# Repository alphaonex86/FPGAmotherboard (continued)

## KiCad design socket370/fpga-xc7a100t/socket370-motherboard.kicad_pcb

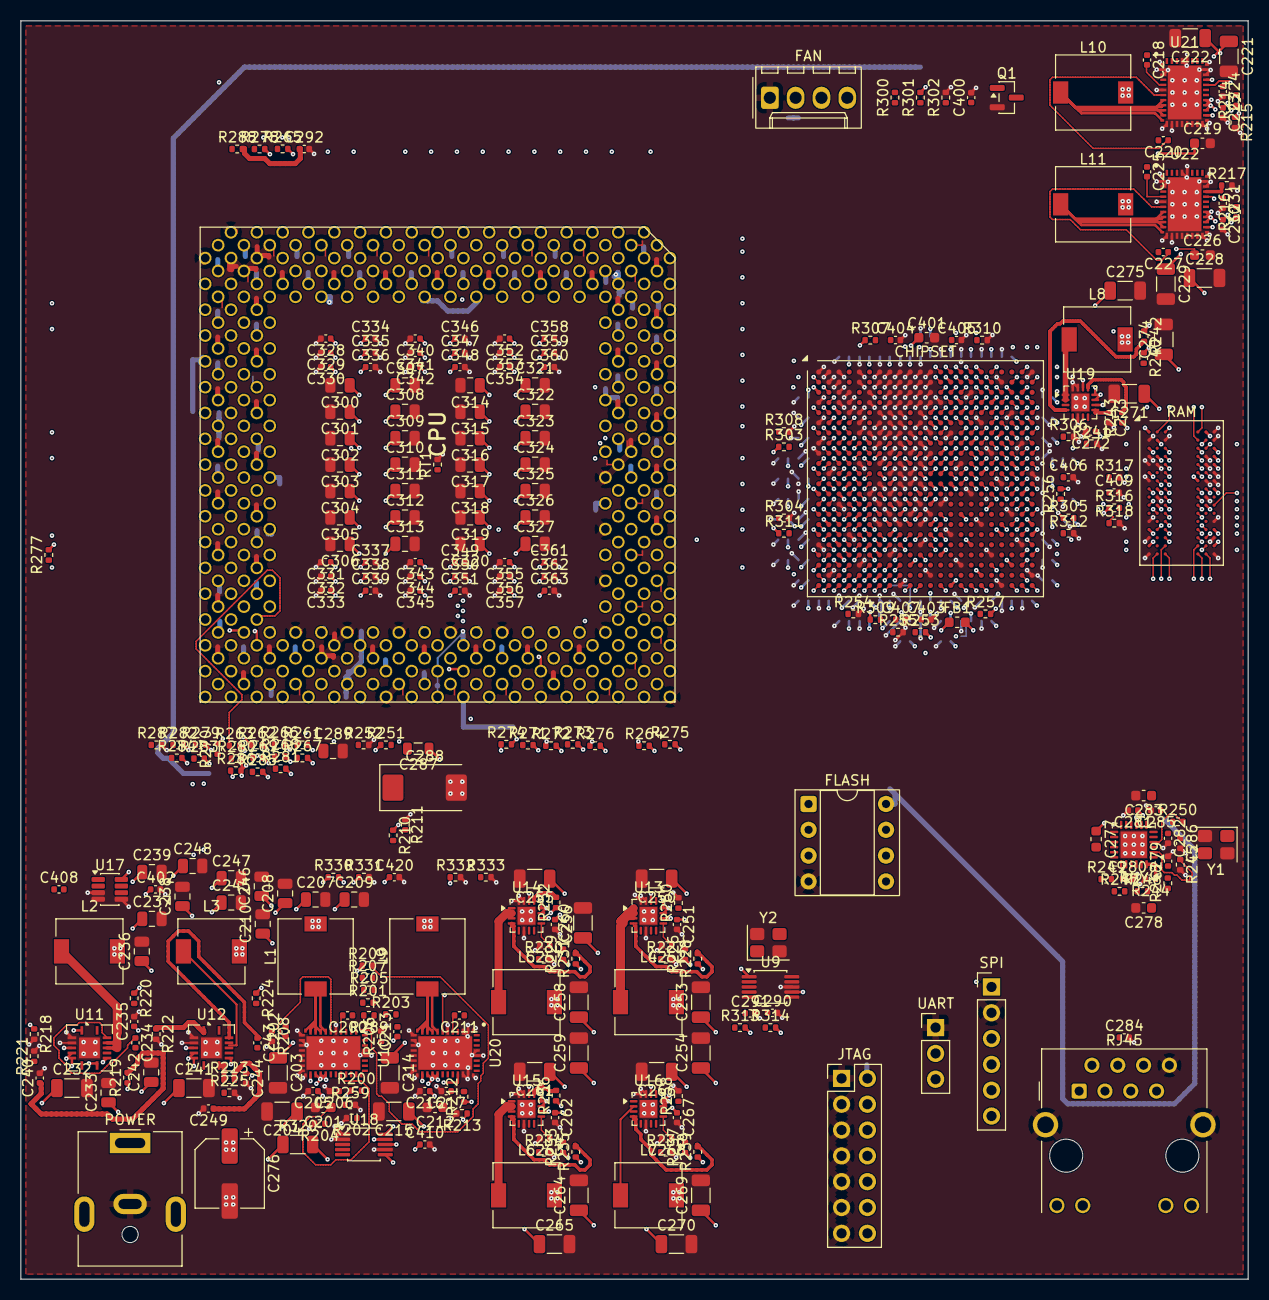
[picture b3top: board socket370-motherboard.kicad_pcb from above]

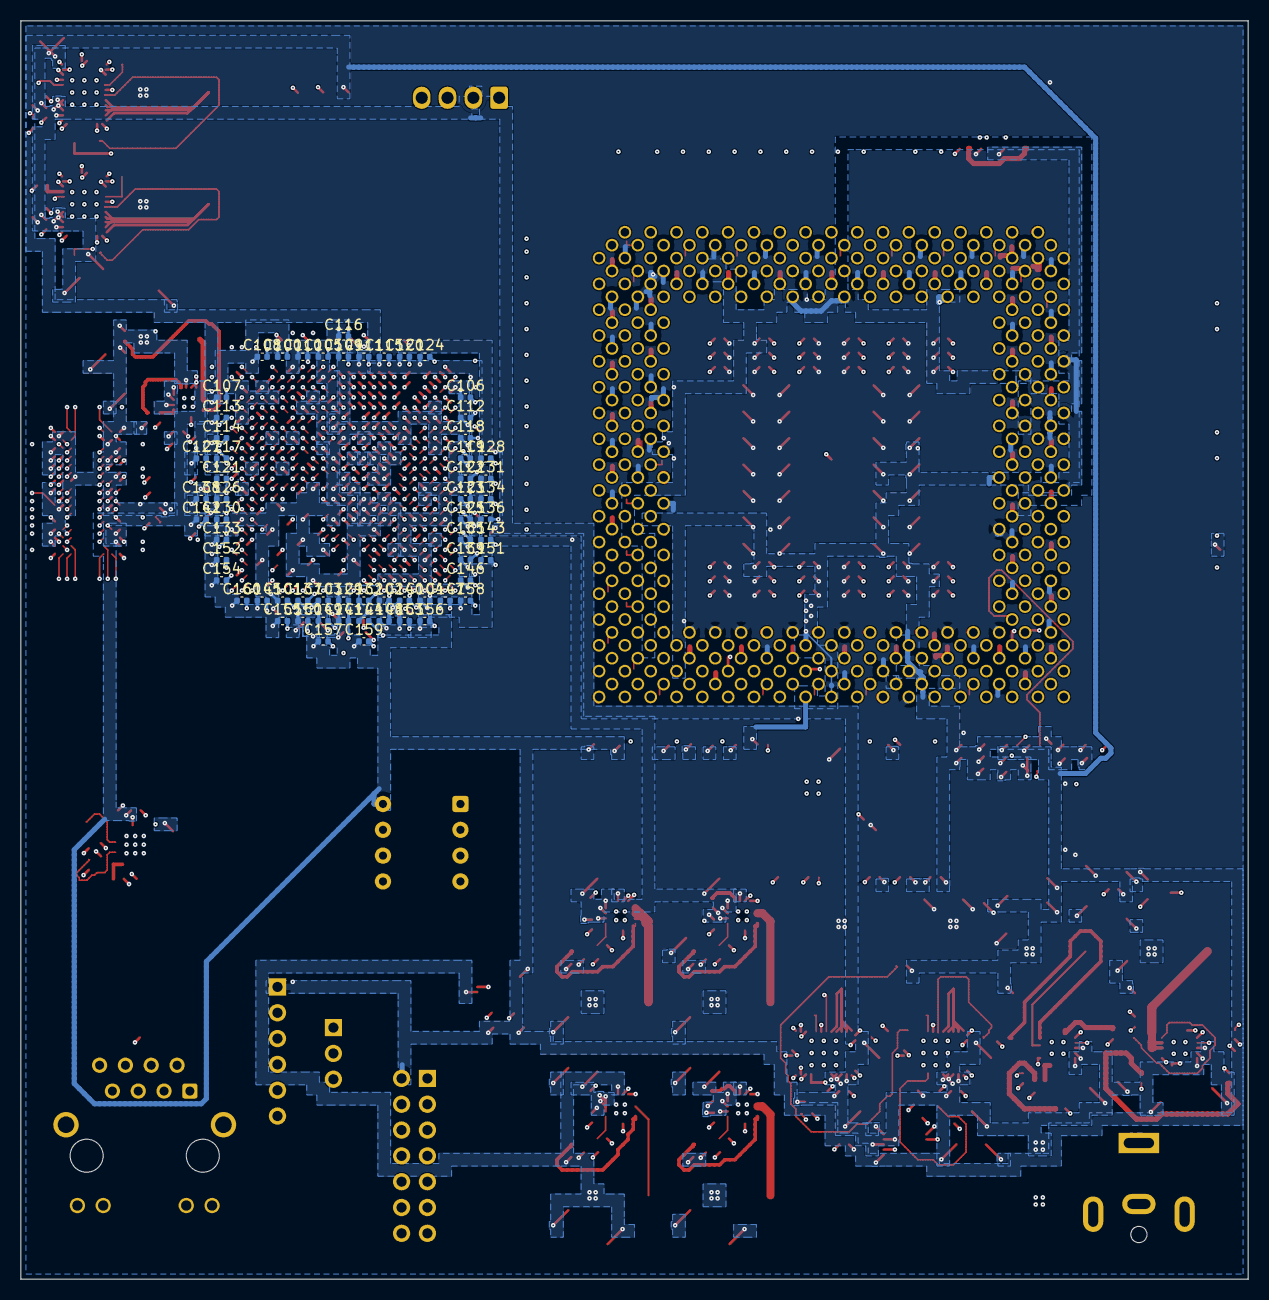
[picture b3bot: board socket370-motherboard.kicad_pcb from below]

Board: 8 copper layers, 120.8 x 123.8 mm, 384 parts (61 on the bottom side), 348 nets.

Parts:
C100, C101, C102, C103, C104, C105, C106, C107, C108, C109, C110, C111, C112, C113, C114, C115, C116, C117, C118, C119, C120, C121, C122, C123, C124, C125, C126, C127, C128, C129, C130, C131, C132, C133, C134, C135, C136, C137, C138, C139, C140, C141, C142, C143, C144, C145, C146, C147, C148, C149, C150, C151, C152, C153, C154, C155, C156, C157, C158, C159, C160: 470nF; C_0402_1005Metric
C200, C211, C218, C225: 1uF 16V X6S; C_0402_1005Metric
C201, C212, C219, C226: 4.7uF 16V X5R; C_0603_1608Metric
C202, C213, C220, C227: 100nF 16V X5R; C_0402_1005Metric
C203, C204, C214, C215, C221, C222, C228, C229, C232, C241, C250, C253, C254, C255, C258, C259, C260, C261, C264, C265, C266, C269, C270, C271, C274, C275: 22uF 25V X5R; C_1206_3216Metric
C205, C216, C223, C230, C235, C244, C403, C404, C405, C406, C407: 10nF 50V X7R; C_0402_1005Metric
C206, C217, C224, C231: 1uF 25V X5R; C_0402_1005Metric
C207, C208, C209, C210, C245, C246, C247, C248: 47uF 6.3V X5R; C_0805_2012Metric
C233, C242: 4.7uF 25V X7R; C_0805_2012Metric
C234, C243, C251, C256, C262, C267, C272, C279, C280, C281, C284, C402, C409, C410, C420: 100nF 16V X7R; C_0402_1005Metric
C236, C237, C238, C239: 47uF 10V X5R; C_0805_2012Metric
C240, C249: 8.2nF 50V X7R; C_0402_1005Metric
C252, C257, C263, C268, C273: 3.3nF 50V X7R; C_0402_1005Metric
C276: 100uF 25V; CP_Elec_6.3x7.7
C277: 600R@100MHz bead; L_0603_1608Metric
C278: 10uF 10V X5R; C_0603_1608Metric
C282: 470pF 50V C0G; C_0402_1005Metric
C283: 1uF 16V X7R; C_0603_1608Metric
C285, C286: 15pF 50V C0G; C_0402_1005Metric
C287: 4.7uH 30mA shielded; L_0805_2012Metric
C288: 33uF 20V tantalum; CP_EIA-7343-31_Kemet-D
C289: 4.7uF 16V X7R; C_0805_2012Metric
C290, C291: 4pF 50V C0G; C_0402_1005Metric
C292: 10pF 50V C0G; C_0402_1005Metric
C300, C301, C302, C303, C304, C305, C306, C307, C308, C309, C310, C311, C312, C313, C314, C315, C316, C317, C318, C319, C320, C321, C322, C323, C324, C325, C326, C327: 22uF; C_0805_2012Metric
C328, C329, C330, C331, C332, C333, C334, C335, C336, C337, C338, C339, C340, C341, C342, C343, C344, C345, C346, C347, C348, C349, C350, C351, C352, C353, C354, C355, C356, C357, C358, C359, C360, C361, C362, C363: 100nF; C_0402_1005Metric
C400: 1nF 50V C0G; C_0402_1005Metric
C401: 470nF 50V X7R; C_0603_1608Metric
C408: 100pF 50V C0G; C_0402_1005Metric
FB1: 600R@100MHz bead; L_0603_1608Metric
J1: HR911105A; RJ45_Hanrun_HR911105A_Horizontal
J2: PJ-063AH; BarrelJack_CUI_PJ-063AH_Horizontal
J3: JTAG; PinHeader_2x07_P2.54mm_Vertical
J4: UART; PinHeader_1x03_P2.54mm_Vertical
J5: SPI ISP; PinHeader_1x06_P2.54mm_Vertical
J6: fan 4-pin 1GND 2+12V 3TACH 4PWM; Molex_KK-254_AE-6410-04A_1x04_P2.54mm_Vertical
L1: VCORE ph1; L_7.3x7.3_H4.5
L2: 5V 6A; L_6.3x6.3_H3
L3: 3V3; L_6.3x6.3_H3
L4: VTT1V5; L_6.3x6.3_H3
L5: VCCINT1V0; L_6.3x6.3_H3
L6: VCCIO1V8; L_6.3x6.3_H3
L7: VCC2V5; L_6.3x6.3_H3
L8: 1V35 out; L_6.3x6.3_H3
L9: VCORE ph2; L_7.3x7.3_H4.5
L10: VCORE ph3; L_7.3x7.3_H4.5
L11: VCORE ph4; L_7.3x7.3_H4.5
Q1: BSS138; SOT-23
R200, R212, R214, R216: 10R 1%; R_0402_1005Metric
R201, R202: 17.8k 1%; R_0402_1005Metric
R203: 162k 1%; R_0402_1005Metric
R204, R215: 82.5k 1%; R_0402_1005Metric
R205, R237: 21.5k 1%; R_0402_1005Metric
R206, R208: 4.64k 1%; R_0402_1005Metric
R207: 1.27k 1%; R_0402_1005Metric
R209, R221, R225, R227, R230, R234, R238, R241, R245, R264, R301, R302, R305, R309, R313, R314: 10k 1%; R_0402_1005Metric
R210: 140R 1%; R_0402_1005Metric
R211: 0R; R_0402_1005Metric
R213: 8.25k 1%; R_0402_1005Metric
R217: 38.3k 1%; R_0402_1005Metric
R218, R222, R228, R231, R232, R235, R236, R239, R242, R243: 100k 1%; R_0402_1005Metric
R219, R223, R300: 1.69k 1%; R_0402_1005Metric
R220: 52.3k 1%; R_0402_1005Metric
R224: 31.6k 1%; R_0402_1005Metric
R226: 8.66k 1%; R_0402_1005Metric
R229, R308, R312: 2.49k 1%; R_0402_1005Metric
R233, R307: 12.4k 1%; R_0402_1005Metric
R240: 6.81k 1%; R_0402_1005Metric
R244: 12.1k 1%; R_0402_1005Metric
R246, R247, R248, R249: 49.9 1%; R_0402_1005Metric
R250, R258, R259, R260: 500R 1%; R_0402_1005Metric
R251, R252, R261, R266, R267, R268, R269, R270, R271, R272, R273, R274, R275, R279, R280, R281, R284, R285, R331: 150R 1%; R_0402_1005Metric
R253, R254, R255, R262, R263, R282, R286, R289, R316, R317: 1k 1%; R_0402_1005Metric
R256, R257, R303, R304, R306, R310: 4.02k 1%; R_0402_1005Metric
R265: 51R 1%; R_0402_1005Metric
R276, R283, R318: 240R 1%; R_0402_1005Metric
R277: 330R 1%; R_0402_1005Metric
R278: 91R 1%; R_0402_1005Metric
R287: 680R 1%; R_0402_1005Metric
R288: 22R 1%; R_0402_1005Metric
R311: 30.9k 1%; R_0402_1005Metric
R320: 10mR 1% 1W; R_1206_3216Metric
R330: 75R 1%; R_0402_1005Metric
R332, R333: 110R 1%; R_0402_1005Metric
RT1: 10k NTC 1% B3380; R_0402_1005Metric
U2: XC7A100T-2FGG484I; Xilinx_FGG484
U3: MT41K128M16JT-125; FBGA-96_8x14mm_Layout9x16_P0.8mm
U7: W25Q64JVDAIQ (DIP-8, socketed); DIP-8_W7.62mm_Socket
U8: LAN8720A-CP-TR; QFN-24-1EP_4x4mm_P0.5mm_EP2.6x2.6mm
U9: SI5351A-B-GTR; MSOP-10_3x3mm_P0.5mm
U10, U20, U21, U22: TPS546B24ARVFR; Texas_RVF0040A_LQFN-CLIP-40_5x7mm_P0.5mm
U11, U12: TPS54620RGYR; Texas_S-PVQFN-N14
U13, U14, U15, U16: TPS62130RGTR; QFN-16-1EP_3x3mm_P0.5mm_EP1.75x1.75mm
U17: TMP421AIDCNR; SOT-23-8
U18: INA226AIDGSR; MSOP-10_3x3mm_P0.5mm
U19: TPS62130RGTR 1V35; QFN-16-1EP_3x3mm_P0.5mm_EP1.75x1.75mm
XU1: PGA370 ZIF; PGA370_Socket_ZIF
Y1, Y2: 25MHz; Crystal_SMD_3225-4Pin_3.2x2.5mm

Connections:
+1V0: C115.1, C119.1, C120.1, C123.1, C124.1, C128.1, C129.1, C131.1, C135.1, C137.1, C139.1, C140.1, C143.1, C147.1, C148.1, C149.1, C153.1, C258.1, C259.1, C260.1, L5.2, R229.1, R231.1, U2.H8, U2.H10, U2.J7, U2.J9, U2.J11, U2.K8, U2.L7, U2.L11, U2.M8, U2.N7, U2.N11, U2.P8, U2.P10, U2.R7, U2.R9, U2.T8, U2.T10, U14.14
+1V8: C100.1, C102.1, C104.1, C105.1, C106.1, C107.1, C108.1, C109.1, C110.1, C112.1, C113.1, C116.1, C118.1, C122.1, C126.1, C132.1, C134.1, C136.1, C141.1, C144.1, C146.1, C151.1, C156.1, C158.1, C264.1, C265.1, FB1.1, L6.2, R233.1, R235.1, U2.A17, U2.AA7, U2.AB4, U2.B14, U2.C1, U2.C21, U2.D18, U2.E12, U2.E15, U2.F2, U2.F22, U2.H6, U2.H12, U2.J3, U2.K12, U2.M4, U2.M12, U2.N1, U2.P12, U2.R5, U2.R11, U2.T2, U2.V6, U2.W3, U15.14
+1V8_ADC: C125.1, C401.1, FB1.2, U2.K10
+1V35: C114.1, C117.1, C121.1, C127.1, C130.1, C138.1, C274.1, C275.1, L8.2, R240.1, R242.1, R316.1, U2.G19, U2.H16, U2.J13, U2.K20, U2.L17, U2.N21, U3.A1, U3.A8, U3.B2, U3.C1, U3.C9, U3.D2, U3.D9, U3.E9, U3.F1, U3.G7, U3.H2, U3.H9, U3.K2, U3.K8, U3.N1, U3.N9, U3.R1, U3.R9, U19.14
+2V5: C269.1, C270.1, L7.2, R237.1, R239.1, R251.1, R277.2, U9.7, U16.14, XU1.Z36 (VCC2.5)
+3V3: C101.1, C103.1, C111.1, C133.1, C142.1, C145.1, C150.1, C152.1, C154.1, C155.1, C157.1, C159.1, C160.1, C245.1, C246.1, C247.1, C248.1, C277.1, C281.1, C402.1, C410.1, J3.2, J5.1, L3.2, R209.1, R224.1, R253.2, R256.2, R257.2, R262.2, R263.2, R264.2, R301.2, R305.1, R309.1, R313.2, R314.2, U2.AA17, U2.AB14, U2.F12, U2.M14, U2.P18, U2.R15, U2.T12, U2.T22, U2.U8, U2.U19, U2.U22, U2.V16, U2.W13, U2.Y10, U2.Y20, U7.8, U8.9, U9.1, U17.8, U18.6
+5V: C236.1, C237.1, C238.1, C239.1, C250.1, C251.1, C255.1, C256.1, C261.1, C262.1, C266.1, C267.1, C271.1, C272.1, L2.2, R220.1, R232.1, R236.1, R243.1, R307.1, U13.10, U13.11, U13.12, U14.10, U14.11, U14.12, U15.10, U15.11, U15.12, U16.10, U16.11, U16.12, U19.10, U19.11, U19.12
+12V: C203.1, C204.1, C205.1, C214.1, C215.1, C216.1, C221.1, C222.1, C223.1, C228.1, C229.1, C230.1, C232.1, C233.1, C241.1, C242.1, C276.1, J6.2, R200.1, R212.1, R214.1, R216.1, R311.1, R320.2, U10.22, U10.23, U10.24, U10.25, U11.4, U11.5, U11.6, U12.4, U12.5, U12.6, U18.8, U18.9, U20.22, U20.23, U20.24, U20.25, U21.22, U21.23, U21.24, U21.25, U22.22, U22.23, U22.24, U22.25
+12V_IN: J2.1, R320.1, U18.10
GND: C100.2, C101.2, C102.2, C103.2, C104.2, C105.2, C106.2, C107.2, C108.2, C109.2, C110.2, C111.2, C112.2, C113.2, C114.2, C115.2, C116.2, C117.2, C118.2, C119.2, C120.2, C121.2, C122.2, C123.2, C124.2, C125.2, C126.2, C127.2, C128.2, C129.2, C130.2, C131.2, C132.2, C133.2, C134.2, C135.2, C136.2, C137.2, C138.2, C139.2, C140.2, C141.2, C142.2, C143.2, C144.2, C145.2, C146.2, C147.2, C148.2, C149.2, C150.2, C151.2, C152.2, C153.2, C154.2, C155.2, C156.2, C157.2, C158.2, C159.2, C160.2, C201.2, C203.2, C204.2, C205.2, C206.2, C207.2, C208.2, C209.2, C210.2, C212.2, C214.2, C215.2, C216.2, C217.2, C219.2, C221.2, C222.2, C223.2, C224.2, C226.2, C228.2, C229.2, C230.2, C231.2, C232.2, C233.2, C235.2, C236.2, C237.2, C238.2, C239.2, C240.2, C241.2, C242.2, C244.2, C245.2, C246.2, C247.2, C248.2, C249.2, C250.2, C251.2, C252.2, C253.2, C254.2, C255.2, C256.2, C257.2, C258.2, C259.2, C260.2, C261.2, C262.2, C263.2, C264.2, C265.2, C266.2, C267.2, C268.2, C269.2, C270.2, C271.2, C272.2, C273.2, C274.2, C275.2, C276.2, C278.2, C279.2, C280.2, C281.2, C282.2, C283.2, C284.2, C285.2, C286.2, C288.2, C289.2, C290.2, C291.2, C292.2, C300.2, C301.2, C302.2, C303.2, C304.2, C305.2, C306.2, C307.2, C308.2, C309.2, C310.2, C311.2, C312.2, C313.2, C314.2, C315.2, C316.2, C317.2, C318.2, C319.2, C320.2, C321.2, C322.2, C323.2, C324.2, C325.2, C326.2, C327.2, C328.2, C329.2, C330.2, C331.2, C332.2, C333.2, C334.2, C335.2, C336.2, C337.2, C338.2, C339.2, C340.2, C341.2, C342.2, C343.2, C344.2, C345.2, C346.2, C347.2, C348.2, C349.2, C350.2, C351.2, C352.2, C353.2, C354.2, C355.2, C356.2, C357.2, C358.2, C359.2, C360.2, C361.2, C362.2, C363.2, C400.2, C401.2, C402.2, C403.2, C404.2, C405.2, C406.2, C407.2, C409.2, C410.2, C420.2, J1.8, J1.SH, J2.2, J3.1, J3.3, J3.5, J3.7, J3.9, J3.11, J3.13, J4.1, J5.2, J6.1, Q1.2, R202.2, R204.2, R206.2, R208.2, R211.1, R213.2, R215.2, R217.2, R218.2, R221.2, R222.2, R225.2, R227.2, R230.2, R234.2, R238.2, R241.2, R244.2, R245.2, R252.2, R254.2, R255.2, R258.2, R259.2, R260.2, R287.2, R302.2, R304.2, R306.2, R308.2, R310.2, R312.2, R317.2, R318.2, R331.2, R332.2, R333.2, RT1.2, U2.A1, U2.A2, U2.A3, U2.A5, U2.A7, U2.A8, U2.A9, U2.A10, U2.A11, U2.A12, U2.A22, U2.AA2, U2.AA12, U2.AA22, U2.AB9, U2.AB19, U2.B2, U2.B3, U2.B5, U2.B7, U2.B8, U2.B9, U2.B10, U2.B11, U2.B12, U2.B19, U2.C3, U2.C4, U2.C6, U2.C8, U2.C9, U2.C10, U2.C11, U2.C12, U2.C16, U2.D1, U2.D3, U2.D4, U2.D6, U2.D8, U2.D9, U2.D10, U2.D11, U2.D12, U2.D13, U2.E4, U2.E5, U2.E7, U2.E8, U2.E9, U2.E11, U2.E20, U2.F1, U2.F5, U2.F7, U2.F8, U2.F9, U2.F11, U2.F17, U2.G5, U2.G6, U2.G7, U2.G8, U2.G9, U2.G10, U2.G12, U2.G14, U2.H1, U2.H7, U2.H9, U2.H11, U2.H21, U2.J1, U2.J8, U2.J10, U2.J12, U2.J18, U2.K5, U2.K7, U2.K9, U2.K11, U2.K15, U2.L2, U2.L8, U2.L9, U2.L10, U2.L22, U2.M7, U2.M9, U2.M10, U2.M11, U2.M19, U2.N6, U2.N8, U2.N16, U2.P3, U2.P7, U2.P9, U2.P11, U2.P13, U2.R8, U2.R10, U2.R12, U2.R20, U2.T7, U2.T9, U2.T11, U2.T17, U2.U4, U2.U14, U2.V1, U2.V11, U2.V21, U2.W8, U2.W18, U2.Y5, U2.Y15, U3.A9, U3.B1, U3.B3, U3.B9, U3.D1, U3.D8, U3.E1, U3.E2, U3.E8, U3.F9, U3.G1, U3.G8, U3.G9, U3.J2, U3.J8, U3.M1, U3.M9, U3.P1, U3.P9, U3.T1, U3.T9, U7.4, U8.25, U9.8, U10.6, U10.13, U10.14, U10.15, U10.16, U10.17, U10.18, U10.19, U10.20, U10.21, U10.36, U10.37, U10.41, U11.2, U11.3, U11.15, U12.2, U12.3, U12.15, U13.6, U13.15, U13.16, U13.17, U14.6, U14.15, U14.16, U14.17, U15.6, U15.15, U15.16, U15.17, U16.6, U16.15, U16.16, U16.17, U17.3, U17.4, U17.5, U18.1, U18.2, U18.7, U19.6, U19.15, U19.16, U19.17, U20.1, U20.2, U20.3, U20.6, U20.13, U20.14, U20.15, U20.16, U20.17, U20.18, U20.19, U20.20, U20.21, U20.30, U20.31, U20.32, U20.36, U20.37, U20.41, U21.1, U21.2, U21.3, U21.6, U21.13, U21.14, U21.15, U21.16, U21.17, U21.18, U21.19, U21.20, U21.21, U21.30, U21.31, U21.32, U21.36, U21.37, U21.41, U22.1, U22.2, U22.3, U22.6, U22.13, U22.14, U22.15, U22.16, U22.17, U22.18, U22.19, U22.20, U22.21, U22.30, U22.31, U22.32, U22.36, U22.37, U22.41, XU1.A37 (GND), XU1.AB32 (GND), XU1.AC5 (GND), XU1.AC33 (GND), XU1.AD2 (GND), XU1.AD34 (GND), XU1.AF32 (GND), XU1.AF36 (GND), XU1.AG5 (GND), XU1.AH2 (GND), XU1.AH34 (GND), XU1.AJ3 (GND), XU1.AJ7 (GND), XU1.AJ11 (GND), XU1.AJ15 (GND), XU1.AJ19 (GND), XU1.AJ23 (GND), XU1.AJ27 (GND), XU1.AK4 (GND), XU1.AK36 (GND), XU1.AL1 (GND), XU1.AL3 (GND), XU1.AM6 (GND), XU1.AM10 (GND), XU1.AM14 (GND), XU1.AM18 (GND), XU1.AM22 (GND), XU1.AM26 (GND), XU1.AM30 (GND), XU1.AM34 (GND), XU1.AN3 (GND), XU1.B4 (GND), XU1.B8 (GND), XU1.B12 (GND), XU1.B16 (GND), XU1.B20 (GND), XU1.B24 (GND), XU1.B28 (GND), XU1.B32 (GND), XU1.D2 (GND), XU1.D4 (GND), XU1.D18 (GND), XU1.D22 (GND), XU1.D26 (GND), XU1.D30 (GND), XU1.D34 (GND), XU1.E7 (GND), XU1.E11 (GND), XU1.E15 (GND), XU1.E19 (GND), XU1.F20 (GND), XU1.F24 (GND), XU1.F28 (GND), XU1.F32 (GND), XU1.F36 (GND), XU1.G5 (GND), XU1.H2 (GND), XU1.H34 (GND), XU1.K36 (GND), XU1.L5 (GND), XU1.M2 (GND), XU1.M34 (GND), XU1.P32 (GND), XU1.P36 (GND), XU1.Q5 (GND), XU1.R34 (GND), XU1.T32 (GND), XU1.T36 (GND), XU1.U5 (GND), XU1.V2 (GND), XU1.V34 (GND), XU1.X32 (GND), XU1.X36 (GND), XU1.Y5 (GND), XU1.Y37 (GND), XU1.Z2 (GND), XU1.Z34 (GND), Y1.2, Y1.4, Y2.2, Y2.4
VCORE: C207.1, C208.1, C209.1, C210.1, C287.1, C300.1, C301.1, C305.1, C306.1, C307.1, C308.1, C309.1, C311.1, C314.1, C315.1, C316.1, C317.1, C318.1, C319.1, C320.1, C321.1, C322.1, C323.1, C324.1, C325.1, C326.1, C327.1, C331.1, C333.1, C334.1, C335.1, C336.1, C338.1, C339.1, C340.1, C341.1, C342.1, C343.1, C344.1, C345.1, C346.1, C347.1, C348.1, C353.1, C354.1, C356.1, C357.1, C358.1, C359.1, C360.1, C361.1, C362.1, C363.1, L1.2, L9.2, L10.2, L11.2, R210.1, R265.2, R303.1, XU1.AA5 (VCCCORE), XU1.AA37 (VCCCORE), XU1.AB2 (VCCCORE), XU1.AB34 (VCCCORE), XU1.AD32 (VCCCORE), XU1.AE5 (VCCCORE), XU1.AF2 (VCCCORE), XU1.AF34 (VCCCORE), XU1.AH24 (VCCCORE), XU1.AH32 (VCCCORE), XU1.AH36 (VCCCORE), XU1.AJ5 (VCCCORE), XU1.AJ9 (VCCCORE), XU1.AJ13 (VCCCORE), XU1.AJ17 (VCCCORE), XU1.AJ21 (VCCCORE), XU1.AJ25 (VCCCORE), XU1.AJ29 (VCCCORE), XU1.AK2 (VCCCORE), XU1.AK34 (VCCCORE), XU1.AM4 (VCCCORE), XU1.AM8 (VCCCORE), XU1.AM12 (VCCCORE), XU1.AM16 (VCCCORE), XU1.AM20 (VCCCORE), XU1.AM24 (VCCCORE), XU1.AM28 (VCCCORE), XU1.AM32 (VCCCORE), XU1.B6 (VCCCORE), XU1.B10 (VCCCORE), XU1.B14 (VCCCORE), XU1.B18 (VCCCORE), XU1.B22 (VCCCORE), XU1.B26 (VCCCORE), XU1.B30 (VCCCORE), XU1.B34 (VCCCORE), XU1.C3 (VCCCORE), XU1.D6 (VCCCORE), XU1.D20 (VCCCORE), XU1.D24 (VCCCORE), XU1.D28 (VCCCORE), XU1.D32 (VCCCORE), XU1.D36 (VCCCORE), XU1.E5 (VCCCORE), XU1.E9 (VCCCORE), XU1.E13 (VCCCORE), XU1.E17 (VCCCORE), XU1.F2 (VCCCORE), XU1.F4 (VCCCORE), XU1.F14 (VCCCORE), XU1.F22 (VCCCORE), XU1.F26 (VCCCORE), XU1.F30 (VCCCORE), XU1.F34 (VCCCORE), XU1.H32 (VCCCORE), XU1.H36 (VCCCORE), XU1.J5 (VCCCORE), XU1.K2 (VCCCORE), XU1.K32 (VCCCORE), XU1.K34 (VCCCORE), XU1.M32 (VCCCORE), XU1.N5 (VCCCORE), XU1.P2 (VCCCORE), XU1.P34 (VCCCORE), XU1.R32 (VCCCORE), XU1.R36 (VCCCORE), XU1.S5 (VCCCORE), XU1.T2 (VCCCORE), XU1.T34 (VCCCORE), XU1.V32 (VCCCORE), XU1.V36 (VCCCORE), XU1.W5 (VCCCORE), XU1.Y35 (VCCCORE), XU1.Z32 (VCCCORE)
VREF1V0: C328.1, C329.1, C330.1, C352.1, C420.1, R330.2, R331.1, U2.C20, U2.D15, U2.E3, U2.N3, U2.V3, U2.W7, XU1.AD6 (VREF), XU1.AK12 (VREF), XU1.AK22 (VREF), XU1.E33 (VREF), XU1.F18 (VREF), XU1.K4 (VREF), XU1.R6 (VREF), XU1.V6 (VREF)
VTT1V5: C253.1, C254.1, C302.1, C303.1, C304.1, C310.1, C312.1, C313.1, C332.1, C337.1, C349.1, C350.1, C351.1, C355.1, L4.2, R226.1, R228.1, R261.2, R266.2, R267.2, R268.2, R269.2, R270.2, R271.2, R272.2, R273.2, R274.2, R275.2, R276.2, R278.2, R279.2, R280.2, R281.2, R282.2, R283.2, R284.2, R285.2, R286.2, R330.1, U13.14, XU1.AA33 (VTT), XU1.AA35 (VTT), XU1.AB36 (VCCCMOS), XU1.AD36 (VCC1), XU1.AH20 (VTT), XU1.AK16 (VTT), XU1.AL13 (VTT), XU1.AL21 (VTT), XU1.AN11 (VTT), XU1.AN15 (VTT), XU1.AN21 (VTT), XU1.E23 (VTT), XU1.G35 (VTT), XU1.S33 (VTT), XU1.S37 (VTT), XU1.U35 (VTT), XU1.U37 (VTT)
cpu_a20m_n: R261.1, U2.A21, XU1.AE33 (A20M#)
cpu_a[3]: U2.AA6, XU1.AK8 (A3#)
cpu_a[4]: U2.Y9, XU1.AH12 (A4#)
cpu_a[5]: U2.Y6, XU1.AH8 (A5#)
cpu_a[6]: U2.AB7, XU1.AN9 (A6#)
cpu_a[7]: U2.T6, XU1.AL15 (A7#)
cpu_a[8]: U2.V8, XU1.AH10 (A8#)
cpu_a[9]: U2.V7, XU1.AL9 (A9#)
cpu_a[10]: U2.V5, XU1.AH6 (A10#)
cpu_a[11]: U2.Y8, XU1.AK10 (A11#)
cpu_a[12]: U2.M6, XU1.AN5 (A12#)
cpu_a[13]: U2.AB5, XU1.AL7 (A13#)
cpu_a[14]: U2.E13, XU1.AK14 (A14#)
cpu_a[15]: U2.T5, XU1.AL5 (A15#)
cpu_a[16]: U2.W6, XU1.AN7 (A16#)
cpu_a[17]: U2.F4, XU1.AE1 (A17#)
cpu_a[18]: U2.J6, XU1.Z6 (A18#)
cpu_a[19]: U2.R4, XU1.AG3 (A19#)
cpu_a[20]: U2.U3, XU1.AC3 (A20#)
cpu_a[21]: U2.H4, XU1.AJ1 (A21#)
cpu_a[22]: U2.P4, XU1.AE3 (A22#)
cpu_a[23]: U2.K6, XU1.AB6 (A23#)
cpu_a[24]: U2.T4, XU1.AB4 (A24#)
cpu_a[25]: U2.L6, XU1.AF6 (A25#)
cpu_a[26]: U2.Y2, XU1.Y3 (A26#)
cpu_a[27]: U2.R2, XU1.AA1 (A27#)
cpu_a[28]: U2.W5, XU1.AK6 (A28#)
cpu_a[29]: U2.J5, XU1.Z4 (A29#)
cpu_a[30]: U2.L4, XU1.AA3 (A30#)
cpu_a[31]: U2.AB3, XU1.AD4 (A31#)
cpu_a[32]: U2.P5, XU1.X6 (A32#)
cpu_a[33]: U2.AA1, XU1.AC1 (A33#)
cpu_a[34]: U2.G4, XU1.W3 (A34#)
cpu_a[35]: U2.N5, XU1.AF4 (A35#)
cpu_ads_n: U2.E22, XU1.AN31 (ADS#)
cpu_bclk: U9.10, XU1.W37 (BCLK)
cpu_binit_n: U2.G21, XU1.B36 (BINIT#)
cpu_bnr_n: U2.C13, XU1.AH14 (BNR#)
cpu_bpri_n: U2.F15, XU1.AN17 (BPRI#)
cpu_br0_n: U2.F20, XU1.AN29 (BR0#)
cpu_bsel[0]: R262.1, XU1.AJ33 (BSEL)
cpu_bsel[1]: R263.1, XU1.AJ31 (BSEL)
cpu_clkref: C289.1, R251.2, R252.1, XU1.Y33 (CLKREF)
cpu_d[0]: U2.R1, XU1.W1 (D0#)
cpu_d[1]: U2.R3, XU1.T4 (D1#)
cpu_d[2]: U2.J2, XU1.N1 (D2#)
cpu_d[3]: U2.H5, XU1.M6 (D3#)
cpu_d[4]: U2.U1, XU1.U1 (D4#)
cpu_d[5]: U2.L3, XU1.S3 (D5#)
cpu_d[6]: U2.V4, XU1.T6 (D6#)
cpu_d[7]: U2.G2, XU1.J1 (D7#)
cpu_d[8]: U2.T1, XU1.S1 (D8#)
cpu_d[9]: U2.Y3, XU1.P6 (D9#)
cpu_d[10]: U2.K3, XU1.Q3 (D10#)
cpu_d[11]: U2.AB1, XU1.M4 (D11#)
cpu_d[12]: U2.G3, XU1.Q1 (D12#)
cpu_d[13]: U2.H2, XU1.L1 (D13#)
cpu_d[14]: U2.W1, XU1.N3 (D14#)
cpu_d[15]: U2.U2, XU1.U3 (D15#)
cpu_d[16]: U2.P2, XU1.H4 (D16#)
cpu_d[17]: U2.V2, XU1.R4 (D17#)
cpu_d[18]: U2.M3, XU1.P4 (D18#)
cpu_d[19]: U2.K4, XU1.H6 (D19#)
cpu_d[20]: U2.N2, XU1.L3 (D20#)
cpu_d[21]: U2.L1, XU1.G1 (D21#)
cpu_d[22]: U2.L5, XU1.F8 (D22#)
cpu_d[23]: U2.F3, XU1.G3 (D23#)
cpu_d[24]: U2.AB2, XU1.K6 (D24#)
cpu_d[25]: U2.K2, XU1.E3 (D25#)
cpu_d[26]: U2.E2, XU1.E1 (D26#)
cpu_d[27]: U2.R6, XU1.F12 (D27#)
cpu_d[28]: U2.H3, XU1.A5 (D28#)
cpu_d[29]: U2.P1, XU1.A3 (D29#)
cpu_d[30]: U2.M2, XU1.J3 (D30#)
cpu_d[31]: U2.Y1, XU1.C5 (D31#)
cpu_d[32]: U2.W2, XU1.F6 (D32#)
cpu_d[33]: U2.D2, XU1.C1 (D33#)
cpu_d[34]: U2.T3, XU1.C7 (D34#)
cpu_d[35]: U2.M1, XU1.B2 (D35#)
cpu_d[36]: U2.W4, XU1.C9 (D36#)
cpu_d[37]: U2.M5, XU1.A9 (D37#)
cpu_d[38]: U2.AA3, XU1.D8 (D38#)
cpu_d[39]: U2.Y4, XU1.D10 (D39#)
cpu_d[40]: U2.Y7, XU1.C15 (D40#)
cpu_d[41]: U2.AB6, XU1.D14 (D41#)
cpu_d[42]: U2.P6, XU1.D12 (D42#)
cpu_d[43]: U2.J4, XU1.A7 (D43#)
cpu_d[44]: U2.AA4, XU1.A11 (D44#)
cpu_d[45]: U2.U5, XU1.C11 (D45#)
cpu_d[46]: U2.A14, XU1.A21 (D46#)
cpu_d[47]: U2.U7, XU1.A15 (D47#)
cpu_d[48]: U2.V9, XU1.A17 (D48#)
cpu_d[49]: U2.U6, XU1.C13 (D49#)
cpu_d[50]: U2.F16, XU1.C25 (D50#)
cpu_d[51]: U2.B17, XU1.A13 (D51#)
cpu_d[52]: U2.AA8, XU1.D16 (D52#)
cpu_d[53]: U2.A15, XU1.A23 (D53#)
cpu_d[54]: U2.D14, XU1.C21 (D54#)
cpu_d[55]: U2.B13, XU1.C19 (D55#)
cpu_d[56]: U2.A18, XU1.C27 (D56#)
cpu_d[57]: U2.A13, XU1.A19 (D57#)
cpu_d[58]: U2.C15, XU1.C23 (D58#)
cpu_d[59]: U2.W9, XU1.C17 (D59#)
cpu_d[60]: U2.D16, XU1.A25 (D60#)
cpu_d[61]: U2.E17, XU1.A27 (D61#)
cpu_d[62]: U2.C17, XU1.E25 (D62#)
cpu_d[63]: U2.AB8, XU1.F16 (D63#)
cpu_dbsy_n: U2.E19, XU1.AL27 (DBSY#)
cpu_defer_n: U2.AA5, XU1.AN19 (DEFER#)
cpu_drdy_n: U2.F19, XU1.AN27 (DRDY#)
cpu_edgctrl: R265.1, XU1.AG1 (EDGCTRL)
cpu_ferr_n: R266.1, U2.F21, XU1.AC35 (FERR#)
cpu_flush_n: R267.1, U2.B22, XU1.AE37 (FLUSH#)
cpu_hit_n: U2.F18, XU1.AL25 (HIT#)
cpu_hitm_n: U2.E18, XU1.AL23 (HITM#)
cpu_ierr_n: R268.1, U2.D22, XU1.AE35 (IERR#)
cpu_ignne_n: R269.1, U2.G22, XU1.AG37 (IGNNE#)
cpu_init_n: R270.1, U2.B20, XU1.AG33 (INIT#)
cpu_lint0: R271.1, U2.F14, XU1.M36 (LINT0/INTR)
cpu_lint1: R272.1, XU1.L37 (LINT1/NMI)
cpu_lock_n: U2.D17, XU1.AK20 (LOCK#)
cpu_picclk: U9.6, XU1.J33 (PICCLK)
cpu_picd[0]: R273.1, XU1.J35 (PICD)
cpu_picd[1]: R274.1, XU1.L35 (PICD)
cpu_pll: C287.2, C288.1, XU1.U33 (PLL), XU1.W33 (PLL)
cpu_prdy_n: R275.1, XU1.A35 (PRDY#)
cpu_preq_n: R276.1, XU1.J37 (PREQ#)
cpu_pres_n: R264.1, XU1.C37 (CPUPRES#)
cpu_pwrgood: R277.1, U2.F13, XU1.AK26 (PWRGOOD)
cpu_req[0]: U2.B16, XU1.AK18 (REQ0#)
cpu_req[1]: U2.E14, XU1.AH16 (REQ1#)
cpu_req[2]: U2.A16, XU1.AH18 (REQ2#)
cpu_req[3]: U2.E16, XU1.AL19 (REQ3#)
cpu_req[4]: U2.B15, XU1.AL17 (REQ4#)
cpu_reset_n: R278.1, R288.1, U2.N4, XU1.AH4 (RESET#), XU1.X4 (RESET2#)
cpu_reset_rc: C292.1, R288.2
cpu_rs[0]: U2.D19, XU1.AH26 (RS0#)
cpu_rs[1]: U2.B18, XU1.AH22 (RS1#)
cpu_rs[2]: U2.D20, XU1.AK28 (RS2#)
cpu_rttctrl: R332.1, XU1.S35 (RTTCTRL)
cpu_slewctrl: R333.1, XU1.E27 (SLEWCTRL)
cpu_slp_n: R279.1, U2.C14, XU1.AH30 (SLP#)
cpu_smi_n: R280.1, U2.D21, XU1.AJ35 (SMI#)
cpu_stpclk_n: R281.1, U2.E21, XU1.AG35 (STPCLK#)
cpu_tck: R282.1, XU1.AL33 (TCK)
cpu_tdi: R283.1, XU1.AN35 (TDI)
cpu_tdo: R284.1, XU1.AN37 (TDO)
cpu_thermdn: C408.2, U17.2, XU1.AL29 (THERMDN)
cpu_thermdp: C408.1, U17.1, XU1.AL31 (THERMDP)
cpu_thermtrip_n: R285.1, U2.C18, XU1.AH28 (THERMTRIP#)
cpu_tms: R286.1, XU1.AK32 (TMS)
cpu_trdy_n: U2.C19, XU1.AN25 (TRDY#)
cpu_trst_n: R287.1, XU1.AN33 (TRST#)
ddr3_a[0]: U2.J17, U3.N3
ddr3_a[1]: U2.L16, U3.P7
ddr3_a[2]: U2.K16, U3.P3
ddr3_a[3]: U2.L13, U3.N2
ddr3_a[4]: U2.M16, U3.P8
ddr3_a[5]: U2.J16, U3.P2
ddr3_a[6]: U2.K14, U3.R8
ddr3_a[7]: U2.J15, U3.R2
ddr3_a[8]: U2.M13, U3.T8
ddr3_a[9]: U2.L15, U3.R3
ddr3_a[10]: U2.N19, U3.L7
ddr3_a[11]: U2.L19, U3.R7
ddr3_a[12]: U2.K17, U3.N7
ddr3_a[13]: U2.K13, U3.T3
ddr3_a[14]: U2.N18, U3.T7
ddr3_ba[0]: U2.L18, U3.M2
ddr3_ba[1]: U2.N20, U3.N8
ddr3_ba[2]: U2.M18, U3.M3
ddr3_cas_n: U2.L20, U3.K3
ddr3_ck_n: U2.K19, U3.K7
ddr3_ck_p: U2.K18, U3.J7
ddr3_cke: U2.M20, U3.K9
ddr3_cs_n: U2.M17, U3.L2
ddr3_dm[0]: U2.H15, U3.E7
ddr3_dm[1]: U2.G20, U3.D3
ddr3_dq[0]: U2.G18, U3.E3
ddr3_dq[1]: U2.H17, U3.F7
ddr3_dq[2]: U2.G17, U3.F2
ddr3_dq[3]: U2.G16, U3.F8
ddr3_dq[4]: U2.H18, U3.H3
ddr3_dq[5]: U2.H13, U3.H8
ddr3_dq[6]: U2.G15, U3.G2
ddr3_dq[7]: U2.G13, U3.H7
ddr3_dq[8]: U2.J19, U3.D7
ddr3_dq[9]: U2.H22, U3.C3
ddr3_dq[10]: U2.J22, U3.C8
ddr3_dq[11]: U2.H19, U3.C2
ddr3_dq[12]: U2.J21, U3.A7
ddr3_dq[13]: U2.H20, U3.A2
ddr3_dq[14]: U2.L21, U3.B8
ddr3_dq[15]: U2.J20, U3.A3
ddr3_dqs_n[0]: U2.H14, U3.G3
ddr3_dqs_n[1]: U2.K22, U3.B7
ddr3_dqs_p[0]: U2.J14, U3.F3
ddr3_dqs_p[1]: U2.K21, U3.C7
ddr3_odt: U2.M21, U3.K1
ddr3_ras_n: U2.M22, U3.J3
ddr3_reset_n: U2.L14, U3.T2
ddr3_vref: C409.1, R316.2, R317.1, U3.H1, U3.M8
ddr3_we_n: U2.M15, U3.L3
ddr3_zq: R318.1, U3.L8
en_vcc2v5: R258.1, U2.AA9, U16.13
en_vcore: R259.1, U2.AB16, U10.27, U20.27, U21.27, U22.27
en_vtt1v5: R260.1, U2.AB17, U13.13
eth_mdc: U2.Y21, U8.13
eth_mdi_rxn: J1.6, R249.1, U8.22
eth_mdi_rxp: J1.3, R248.1, U8.23
eth_mdi_txn: J1.2, R247.1, U8.20
eth_mdi_txp: J1.1, R246.1, U8.21
eth_mdio: U2.T21, U8.12
eth_nintsel: R245.1, U8.2
eth_rbias: R244.1, U8.24
eth_ref_clk: U2.Y18, U8.14
eth_rmii_crs_dv: U2.U21, U8.11
eth_rmii_rx_er: U2.V22, U8.10
eth_rmii_rxd[0]: U2.W21, U8.8
eth_rmii_rxd[1]: U2.W22, U8.7
eth_rmii_tx_en: U2.AB20, U8.16
eth_rmii_txd[0]: U2.AB21, U8.17
eth_rmii_txd[1]: U2.AB22, U8.18
eth_rst_n: U2.AA21, U8.15
eth_vdda: C277.2, C278.1, C279.1, C280.1, C284.1, J1.4, J1.5, R246.2, R247.2, R248.2, R249.2, U8.1, U8.19
eth_vddcr: C282.1, C283.1, U8.6
eth_xtal1: C285.1, U8.5, Y1.1
eth_xtal2: C286.1, R250.1, Y1.3
eth_xtal2_drv: R250.2, U8.4
fan_pwm: J6.4, Q1.3
fan_pwm_g: Q1.1, R302.1, U2.P20
fan_tach: J6.3, R300.1, R301.1
fan_tach_f: C400.1, R300.2, U2.T20
fpga_init_b: R257.1, U2.U12
fpga_m0: R253.1, U2.U11
fpga_m1: R254.1, U2.U10
fpga_m2: R255.1, U2.U9
fpga_program_b: R256.1, U2.N12
fpga_refclk: U2.W11, U9.9
i2c_scl: R313.1, U2.AB10, U9.4, U10.3, U17.7, U18.5
i2c_sda: R314.1, U2.AB11, U9.5, U10.2, U17.6, U18.4
jtag_tck: J3.6, U2.V12
jtag_tdi: J3.10, U2.R13
jtag_tdo: J3.8, U2.U13
jtag_tms: J3.4, U2.T13
spi_clk: J5.4, U2.L12, U7.6
spi_cs_n: J5.3, U2.T19, U7.1
spi_dq0: J5.6, U2.P22, U7.5
spi_dq1: J5.5, U2.R22, U7.2
spi_dq2: U2.P21, U7.3
spi_dq3: U2.R21, U7.7
sw_1v0: L5.1, U14.1, U14.2, U14.3
sw_1v8: L6.1, U15.1, U15.2, U15.3
sw_1v35: L8.1, U19.1, U19.2, U19.3
sw_2v5: L7.1, U16.1, U16.2, U16.3
sw_3v3: C243.2, L3.1, U12.11, U12.12
sw_5v: C234.2, L2.1, U11.11, U11.12
sw_vcore: C202.2, L1.1, U10.8, U10.9, U10.10, U10.11, U10.12
sw_vcore_b: C213.2, L9.1, U20.8, U20.9, U20.10, U20.11, U20.12
sw_vcore_c: C220.2, L10.1, U21.8, U21.9, U21.10, U21.11, U21.12
sw_vcore_d: C227.2, L11.1, U22.8, U22.9, U22.10, U22.11, U22.12
sw_vtt1v5: L4.1, U13.1, U13.2, U13.3
tsen_socket: C404.1, R305.2, R306.1, RT1.1, U2.G1
u9_xa: C290.1, U9.2, Y2.1
u9_xb: C291.1, U9.3, Y2.3
u10_adrsel: R207.2, R208.1, U10.31
u10_avin: C206.1, R200.2, U10.26
u10_boot: C202.1, U10.7
u10_bp1v5: C200.1, R201.1, R203.1, R205.1, R207.1, U10.4
u10_drtn: C200.2, U10.5
u10_msel1: R201.2, R202.1, U10.32
u10_msel2: R203.2, R204.1, U10.29
u10_pgood: R209.2, U10.1
u10_vdd5: C201.1, U10.28
u10_vsel: R205.2, R206.1, U10.30
u11_boot: C234.1, U11.13
u11_comp: R219.1, U11.8
u11_compz: C240.1, R219.2
u11_fb: R220.2, R221.1, U11.7
u11_rt: R218.1, U11.1
u11_ss: C235.1, U11.9
u12_boot: C243.1, U12.13
u12_comp: R223.1, U12.8
u12_compz: C249.1, R223.2
u12_fb: R224.2, R225.1, U12.7
u12_rt: R222.1, U12.1
u12_ss: C244.1, U12.9
u13_fb: R226.2, R227.1, U13.5
u13_pg: R228.2, U13.4
u13_ss: C252.1, U13.9
u14_en: R232.2, U14.13
u14_fb: R229.2, R230.1, U14.5
u14_pg: R231.2, U14.4
u14_ss: C257.1, U14.9
u15_en: R236.2, U15.13
u15_fb: R233.2, R234.1, U15.5
u15_pg: R235.2, U15.4
u15_ss: C263.1, U15.9
u16_fb: R237.2, R238.1, U16.5
u16_pg: R239.2, U16.4
u16_ss: C268.1, U16.9
u19_en: R243.2, U19.13
u19_fb: R240.2, R241.1, U19.5
u19_pg: R242.2, U19.4
u19_ss: C273.1, U19.9
u20_avin: C217.1, R212.2, U20.26
u20_boot: C213.1, U20.7
u20_bp1v5: C211.1, U20.4, U20.34
u20_drtn: C211.2, U20.5
u20_msel2: R213.1, U20.29
u20_vdd5: C212.1, U20.28
u21_avin: C224.1, R214.2, U21.26
u21_boot: C220.1, U21.7
u21_bp1v5: C218.1, U21.4, U21.34
u21_drtn: C218.2, U21.5
u21_msel2: R215.1, U21.29
u21_vdd5: C219.1, U21.28
u22_avin: C231.1, R216.2, U22.26
u22_boot: C227.1, U22.7
u22_bp1v5: C225.1, U22.4, U22.34
u22_drtn: C225.2, U22.5
u22_msel2: R217.1, U22.29
u22_vdd5: C226.1, U22.28
uart_rx: J4.2, U2.AB13
uart_tx: J4.3, U2.AB15
vcore_bcx_clk: U10.39, U20.39, U21.39, U22.39
vcore_bcx_dat: U10.40, U20.40, U21.40, U22.40
vcore_gsense: R211.2, R289.2, U10.34
vcore_sense: R210.2, R289.1, U10.33
vcore_sync: U10.38, U20.38, U21.38, U22.38
vcore_vshare: U10.35, U20.35, U21.35, U22.35
vsen_3v3: C406.1, R309.2, R310.1, U2.K1
vsen_5v: C405.1, R307.2, R308.1, U2.E1
vsen_12v: C407.1, R311.2, R312.1, U2.C2
vsen_vcore: C403.1, R303.2, R304.1, U2.B1
